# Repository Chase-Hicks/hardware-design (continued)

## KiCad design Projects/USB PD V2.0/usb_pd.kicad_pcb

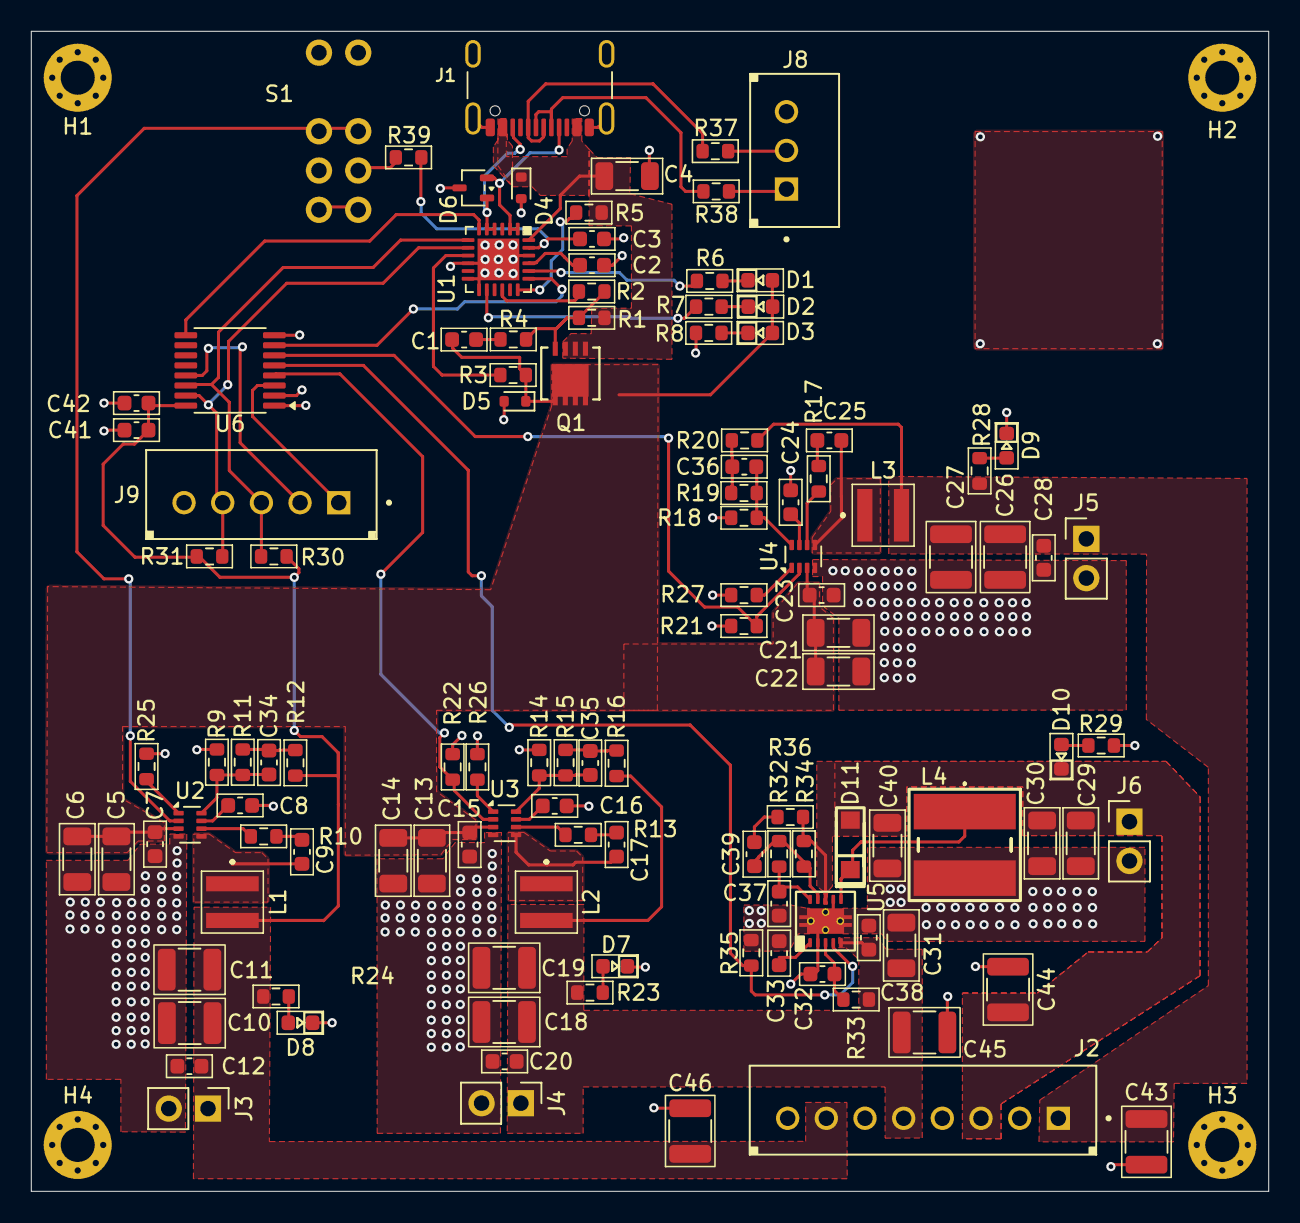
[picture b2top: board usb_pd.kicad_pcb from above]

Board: 2 copper layers, 80.0 x 75.0 mm, 120 parts (0 on the bottom side), 68 nets.

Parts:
C1, C7, C8, C9, C12, C15, C16, C17, C20, C23, C24, C25, C28, C32, C37, C38, C42: 100nF; C_0603_1608Metric
C2, C3, C41: 1uF; C_0603_1608Metric
C4: 4.7uF; C_1206_3216Metric
C5, C6, C13, C14, C21, C22, C29, C30, C31, C40: 10uF; C_1206_3216Metric
C10, C11, C18, C19, C26, C27, C43, C44, C45, C46: 22uF; C_1210_3225Metric
C33: 4.7nF; C_0603_1608Metric
C34, C35, C36, C39: 10pF; C_0603_1608Metric
D1, D7, D8, D9, D10: GRN; LED_0603_1608Metric
D2: YEL; LED_0603_1608Metric
D3: BLUE; LED_0603_1608Metric
D4, D5: ESDA25P35
D6: ESDA25W
D11: SL03; DO-219AB-2
H1, H2, H3, H4: M2; MountingHole_2.2mm_M2_Pad_Via
J1: USB2.0 TYP C 16P; USB_C_Receptacle_GCT_USB4105-xx-A_16P_TopMnt_Horizontal
J2: 8P Header; B8B-XH-A
J3, J4, J5, J6: 2P; PinHeader_1x02_P2.54mm_Vertical
J8: 3P Header; B3B-XH-A
J9: 5P Header; B5B-XH-A
L1: 4.7uH; XAL-4030-xxx
L2, L3: 6.8uH; XEL-4030-xxx
L4: 33uH; LPS6235333MRC
Q1: STL6P3LLH6; POWERFLAT_3P3X3P3_STM
R1, R32, R36: 100k; R_0603_1608Metric
R2, R6, R7, R8, R28, R29: 22k; R_0603_1608Metric
R3, R5: 1k; R_0603_1608Metric
R4, R33: 100; R_0603_1608Metric
R9, R18, R21, R22, R35: 10k; R_0603_1608Metric
R10, R13, R17, R25, R26, R27, R37, R38: 0; R_0603_1608Metric
R11: 31.2k; R_0603_1608Metric
R12, R16, R20: 49.9; R_0603_1608Metric
R14: 10.2k; R_0603_1608Metric
R15: 53.6k; R_0603_1608Metric
R19: 178k; R_0603_1608Metric
R23: 470; R_0603_1608Metric
R24, R39: 330; R_0603_1608Metric
R30, R31: 4.7k; R_0603_1608Metric
R34: 1.24M; R_0603_1608Metric
S1: G12JVCF
U1: STUSB4500QTR; QFN-24-1EP_4x4mm_P0.5mm_EP2.7x2.7mm
U2, U3, U4: TPS62933; SOT-583-8
U5: TPS63700; Texas_DRC0010J_ThermalVias
U6: PCA9538APWJ; TSSOP-16_4.4x5mm_P0.65mm

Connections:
5V_EN: R22.1, U3.2 (EN), U6.4 (IO0)
15V_EN: R21.1, U4.2 (EN), U6.6 (IO2)
+3.3V: C10.1, C11.1, C12.2, C41.2, C42.2, C46.1, J2.7, J3.1, L1.2, R12.2, R24.1, R30.1, R31.1, U6.16 (V_{DD})
+5V: C18.1, C19.1, C20.2, C31.1, C38.2, C45.1, J2.5, J4.1, L2.2, R16.2, R23.1, R33.1, U5.5 (IN)
+15V: C26.1, C27.1, C28.2, C43.1, J2.1, J5.1, L3.2, R20.2, R28.1
+VREG_1V2: C2.2, U1.21 (VREG_1V2)
+VREG_2V7: C3.2, R39.1, U1.23 (VREG_2V7)
+Vbus: C4.1, D4.1 (K), J1.A4 (VBUS), J1.A9 (VBUS), J1.B4 (VBUS), J1.B9 (VBUS), Q1.1 (S), R1.1, R5.1, U1.24 (VDD)
+Vsink: C1.2, C5.1, C6.1, C7.2, C13.1, C14.1, C15.2, C21.1, C22.1, C23.2, D1.2 (A), D2.2 (A), D3.2 (A), D5.1 (K), Q1.3 (D), R3.1, U2.3 (VIN), U3.3 (VIN), U4.3 (VIN)
-15V: C29.1, C30.1, C40.1, C44.1, D10.1 (K), D11.1 (A), J2.3, J6.1, R34.2, R36.2, U5.8 (OUT)
-15V_EN: R35.1, U5.4 (EN), U6.5 (IO1)
/power_delivery/CC1: D6.2 (K), J1.A5 (CC1), U1.1 (CC1DB), U1.2 (CC1)
/power_delivery/CC2: D6.1 (K), J1.B5 (CC2), U1.4 (CC2), U1.5 (CC2DB)
/power_delivery/PD_ALERT: U1.19 (ALERT), U6.7 (IO3)
/power_delivery/PD_RST: U1.6 (RESET), U6.9 (IO4)
/power_delivery/PD_SCA: J9.4, R31.2, U1.8 (SDA), U6.15 (SDA)
/power_delivery/PD_SCL: J9.3, R30.2, U1.7 (SCL), U6.14 (SCL)
/power_delivery/POWER_OK2: R6.2, U1.20 (POWER_OK2)
/power_delivery/POWER_OK3: R7.2, U1.14 (POWER_OK3)
/power_delivery/~PWR_CTRL_INT: J9.2, U6.13 (~INT)
/power_delivery/~PWR_CTRL_RST: J9.1, U6.3 (~RESET)
/power_rails/3V3_EN: S1.3 (Up), S1.6 (K), U2.2 (EN)
GND: C2.1, C3.1, C4.2, C5.2, C6.2, C7.1, C8.1, C10.2, C11.2, C12.1, C13.2, C14.2, C15.1, C16.1, C18.2, C19.2, C20.1, C21.2, C22.2, C23.1, C24.1, C26.2, C27.2, C28.1, C29.2, C30.2, C31.2, C32.1, C33.1, C37.1, C38.1, C40.2, C41.1, C42.1, C43.2, C44.2, C45.2, C46.2, D4.2 (A), D5.2 (A), D6.3 (A), D7.1 (K), D8.1 (K), D9.1 (K), H1.1 (1_1), H2.1 (1_1), H3.1 (1_1), H4.1 (1_1), J1.A1 (GND), J1.A12 (GND), J1.B1 (GND), J1.B12 (GND), J1.S1 (SHIELD), J2.2, J2.4, J2.6, J2.8, J3.2, J4.2, J5.2, J6.2, J8.3, J9.5, L4.2, R8.2, R9.2, R14.2, R18.2, R21.2, R22.2, R25.2, R26.2, R27.2, R29.2, R35.2, S1.2, U1.10 (GND), U1.12 (ADDR0), U1.13 (ADDR1), U1.22 (VSYS), U1.25 (GND), U2.4 (GND), U3.4 (GND), U4.4 (GND), U5.2 (GND), U5.7 (PS_GND), U5.11 (EP), U6.1 (A0), U6.2 (A1), U6.8 (V_{SS})
unnamed: C1.1, R4.2
unnamed: C9.2, R10.2
unnamed: C17.2, R13.2
unnamed: C25.2, R17.2
unnamed: C34.1, R11.2, R12.1
unnamed: C35.1, R15.2, R16.1
unnamed: C36.1, R19.2, R20.1
unnamed: C39.1, R36.1
unnamed: D1.1 (K), R6.1
unnamed: D2.1 (K), R7.1
unnamed: D3.1 (K), R8.1
unnamed: D7.2 (A), R23.2
unnamed: D8.2 (A), R24.2
unnamed: D9.2 (A), R28.2
unnamed: D10.2 (A), R29.1
unnamed: D11.2 (K), L4.1, U5.6 (SW)
unnamed: J8.1, R38.1
unnamed: J8.2, R37.1
unnamed: Q1.2 (G), R1.2, R2.1, R4.1
unnamed: R39.2, S1.5 (A)
unnamed: S1.1 (Down), S1.4 (K)
unnamed: R3.2, U1.9 (DISCH)
unnamed: R2.2, U1.16 (VBUS_EN_SNK)
unnamed: R5.2, U1.18 (VBUS_VS_DISCH)
unnamed: R10.1, U2.6 (BST)
unnamed: C34.2, R9.1, R11.1, U2.8 (FB)
unnamed: R25.1, U2.1 (RT)
unnamed: C8.2, U2.7 (SS)
unnamed: C9.1, L1.1, U2.5 (SW)
unnamed: R13.1, U3.6 (BST)
unnamed: C35.2, R14.1, R15.1, U3.8 (FB)
unnamed: R26.1, U3.1 (RT)
unnamed: C16.2, U3.7 (SS)
unnamed: C17.1, L2.1, U3.5 (SW)
unnamed: R17.1, U4.6 (BST)
unnamed: C36.2, R18.1, R19.1, U4.8 (FB)
unnamed: R27.1, U4.1 (RT)
unnamed: C24.2, U4.7 (SS)
unnamed: C25.1, L3.1, U4.5 (SW)
unnamed: C33.2, U5.1 (COMP)
unnamed: C39.2, R32.2, R34.1, U5.9 (FB)
unnamed: C32.2, R33.2, U5.3 (VIN)
unnamed: C37.2, R32.1, U5.10 (VREF)
USB_DM: J1.A7 (D-), J1.B7 (D-), R38.2
USB_DP: J1.A6 (D+), J1.B6 (D+), R37.2

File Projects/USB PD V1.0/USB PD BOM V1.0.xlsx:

Reference | Qty | Value | MFG | MFG PN | Supplier | Supplier PN | Part Description
C1,C7,C8,C9,C12,C15,C16,C17,C20,C23,C24,C25,C28,C32,C37,C38,C42 | 17 | 100nF????? | Samsung | CL10B104KB8NNWC | Digikey | 1276-1935-1-ND | CAP, 100nF, 50V, X7R, 10%, 0603
C2,C3,C41 | 3 | 1uF | TDK | C1608X7R2A105K080AC | Digikey | 445-C1608X7R2A105K080ACCT-ND | CAP, 1uF, 100V, X7R, 10%, 0603
C4 | 1 | 4.7uF | Murata | GRM31CR71H475KA12K | Digikey | 490-GRM31CR71H475KA12KCT-ND | CAP, 4.7uF, 50V, X7R, 10%, 1206
C5,C6,C13,C14,C21,C22,C29,C30,C31,C40 | 10 | 10uF | Murata | GRM188R61E106KA73D | Digikey | 490-18214-1-ND | CAP, 10uF, 25V, X5R, 10%, 1206
C10,C11,C18,C19,C26,C27,C43,C44,C45,C46 | 10 | 22uF | Samsung | CL32A226KAJNNNE | Digikey | 1276-1101-1-ND | CAP, 22uF, 25V, X5R, 10%, 1210
C33 | 1 | 4.7nF | Yageo | CC0603KRX7R9BB472 | Digikey | 311-1083-1-ND | CAP, 4.7nF, 50V, X7R, 10%, 0603
C34,C35,C36,C39 | 4 | 10pF | Yageo | CC0603JRNPO9BN100 | Digikey | 311-1058-1-ND | CAP, 10pF, 50V, C0G, 5%, 0603
D1,D7,D8,D9,D10 | 5 | GRN | Kingbright | APT1608SGC | Digikey | 754-1121-1-ND | LED, GRN, 2.2V, 0603
D2 | 1 | YEL | Kingbright | APT1608YC | Digikey | 754-1125-1-ND | LED, YELLOW, 2.1V, 0603
D3 | 1 | BLUE | Kingbright | APT1608QBC/D | Digikey | 754-1434-1-ND | LED, BLUE, 3.3V, 0603
D4,D5 | 2 | ESDA25P35 | STMicro | ESDA25P35-1U1M | Digikey | 497-16913-1-ND | D, TVS, 31V, 35A, 1610
D6 | 1 | ESDA25W | STMicro | ESDA25W | Digikey | 497-6689-1-ND | D, ESD, SOD-323
D11 | 1 | SL03 | Vishay | SL03-GS08 | Digikey | SL03-GS08CT-ND | D, SCHOTTKY, 30V, 1.1A, DO-219AB
J1 | 1 | USB2.0 TYP C 16P | GCT | USB4105-GF-A | Digikey | 2073-USB4105-GF-ACT-ND | CONN, USB C, 2.0, 16P
J2 | 1 | 8P Header | JST | B8B-XH-A | Digikey | 455-B8B-XH-A-ND | CONN, HEADER, VERT, 8P, TH, 2.5MM
J8 | 1 | 3P Header | JST | B3B-XH-A | Digikey | 455-2248-ND | CONN, HEADER, VERT, 3P, TH, 2.5MM
J9 | 1 | 5P Header | JST | B5B-XH-A | Digikey | 455-B5B-XH-A-ND | CONN, HEADER, VERT, 5P, TH, 2.5MM
Q1 | 1 | STL6P3LLH6 | STMicro | STL6P3LLH6 | Digikey | 497-15315-1-ND | IC, SMD, PMOS, 30V, 6A
R1,R32,R36 | 3 | 100k | Yageo | RC0603FR-07100KL | Digikey | 311-100KHRCT-ND | RESIST, 100k, 1/10W, 1%, 0603
R2,R6,R7,R8,R28,R29 | 6 | 22k | Yageo | RC0603FR-0722KL | Digikey | 311-22.0KHRCT-ND | RESIST, 22k, 1/10W, 1%, 0603
R3,R5 | 2 | 1k | Yageo | RC0603FR-071KL | Digikey | 311-1.00KHRCT-ND | RESIST, 1k, 1/10W, 1%, 0603
R4,R33 | 2 | 100 | Yageo | RC0603FR-07100RL | Digikey | 311-100HRCT-ND | RESIST, 100, 1/10W, 1%, 0603
R9,R18,R21,R22,R35 | 5 | 10k | Yageo | RC0603FR-0710KL | Digikey | 311-10.0KHRCT-ND | RESIST, 10k, 1/10W, 1%, 0603
R10,R13,R17,R25,R26,R27,R37,R38 | 8 | 0 | Panasonic | ‎ERJ-3GEY0R00V‎ | Digikey | ‎P0.0GCT-ND‎ | RESIST, 0, 1/10W, 0603
R11 | 1 | 31.2k | Yageo | RT0603BRD0731K2L | Digikey | 13-RT0603BRD0731K2LCT-ND | RESIST, 31.2k, 1/10W, 0.1%, 0603
R12,R16,R20 | 3 | 49.9 | Panasonic | ERA-3AEB49R9V | Digikey | P49.9DBCT-ND | RESIST, 49.9, 1/10W, 0.1%, 0603
R14 | 1 | 10.2k | Yageo | RT0603BRD0710K2L | Digikey | YAG1502CT-ND | RESIST, 10.2k, 1/10W, 0.1%, 0603
R15 | 1 | 53.6k | Yageo | RC0603FR-0753K6L | Digikey | 311-53.6KHRCT-ND | RESIST, 53.6k, 1/10W, 1%, 0603
R19 | 1 | 178k | Panasonic | ERA-3AEB1783V | Digikey | P178KDBCT-ND | RESIST, 178k, 1/10W, 0.1%, 0603
R23 | 1 | 470 | Panasonic | ERA-3AED471V | Digikey | P123767CT-ND | RESIST, 470, 1/10W, 1%, 0603
R24,R39 | 2 | 330 | Vishay | MCT06030C3300FP500 | Digikey | MCT0603-330-CFCT-ND | RESIST, 330, 1/10W, 1%, 0603
R30,R31 | 2 | 4.7k | Panasonic | ERA-3AEB472V | DigiKey | P4.7KDBCT-ND | RESIST, 4.7k, 1/10W, 0.1%, 0603
R34 | 1 | 1.24M | Yageo | RC0603FR-071M24L | Digikey | 13-RC0603FR-071M24LCT-ND | RESIST, 1.24M, 1/10W, 1%, 0603
S1 | 1 | G12JVCF | NKK | G12JVCF | Digikey | 360-1765-ND | SW, SPDT, GRN/RED LED
U1 | 1 | STUSB4500QTR | STMicro | STUSB4500QTR | Digikey | 497-18060-1-ND | IC, QFN, PWR, USB PD SINK
U2,U3,U4 | 3 | TPS62933 | TI | TPS62933DRLR | Digikey | 296-TPS62933DRLRCT-ND | IC, SMD, REG, BUCK, STEP-DOWN, 30VIN, 3A
U5 | 1 | TPS63700 | TI | TPS63700DRCR | Digikey | 296-31989-1-ND | IC, REG, SW, INVERT, TPS63700, VSON
U6 | 1 | PCA9538APWJ | NXP | PCA9538APWJ | Digikey | 568-9915-1-ND | IC, I2C, 8 bit, I/O, Expander
x | 1 |  | JST | XHP-3 | DigiKey | 455-2219-ND
x | 1 |  | JST | XHP-5 | DigiKey | 455-2268-ND
x | 1 |  | JST | XHP-8 | DigiKey | 455-1902-ND
